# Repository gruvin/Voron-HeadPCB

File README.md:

# Voron-HeadPCB

## Oldschool wiring harness strapped to the back of the stepper where a CANN bus board might otherwise be.

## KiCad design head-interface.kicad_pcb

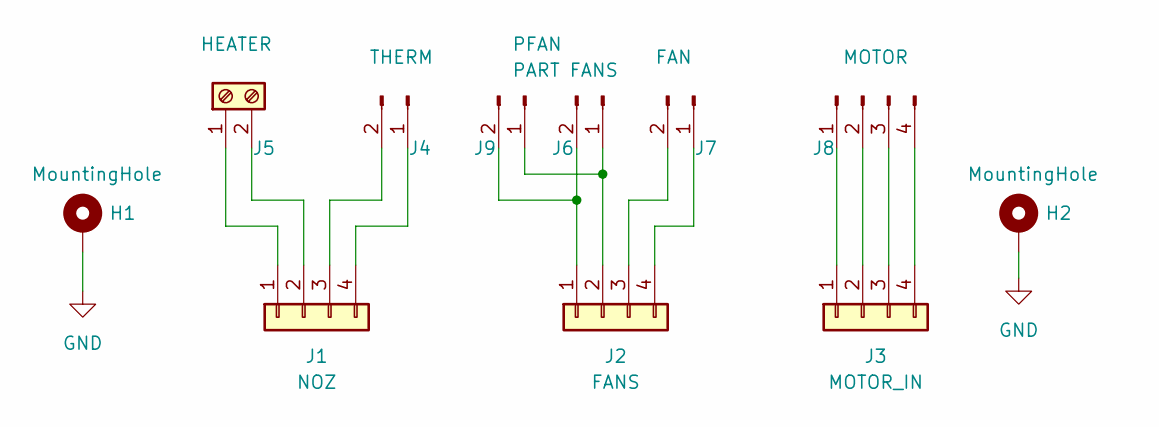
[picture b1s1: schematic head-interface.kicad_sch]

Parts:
H1, H2: MountingHole; MountingHole_3.2mm_M3_Pad
J1: NOZ; JST_EH_B4B-EH-A_1x04_P2.50mm_Vertical
J2: FANS; JST_EH_B4B-EH-A_1x04_P2.50mm_Vertical
J3: MOTOR_IN; JST_EH_B4B-EH-A_1x04_P2.50mm_Vertical
J4: THERM; JST_PH_B2B-PH-K_1x02_P2.00mm_Vertical
J5: HEATER; TerminalBlock_Phoenix_PT-1,5-2-3.5-H_1x02_P3.50mm_Horizontal
J6: PART FANS; JST_PH_B2B-PH-K_1x02_P2.00mm_Vertical
J7: FAN; JST_PH_B2B-PH-K_1x02_P2.00mm_Vertical
J8: MOTOR; JST_EH_B4B-EH-A_1x04_P2.50mm_Vertical
J9: PFAN; JST_PH_B2B-PH-K_1x02_P2.00mm_Vertical

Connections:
GND: H1.1, H2.1
unnamed: J1.1, J5.1
unnamed: J1.2, J5.2
unnamed: J1.3, J4.2
unnamed: J1.4, J4.1
unnamed: J2.1, J6.2, J9.2
unnamed: J2.2, J6.1, J9.1
unnamed: J2.3, J7.2
unnamed: J2.4, J7.1
unnamed: J3.1, J8.1
unnamed: J3.2, J8.2
unnamed: J3.3, J8.3
unnamed: J3.4, J8.4

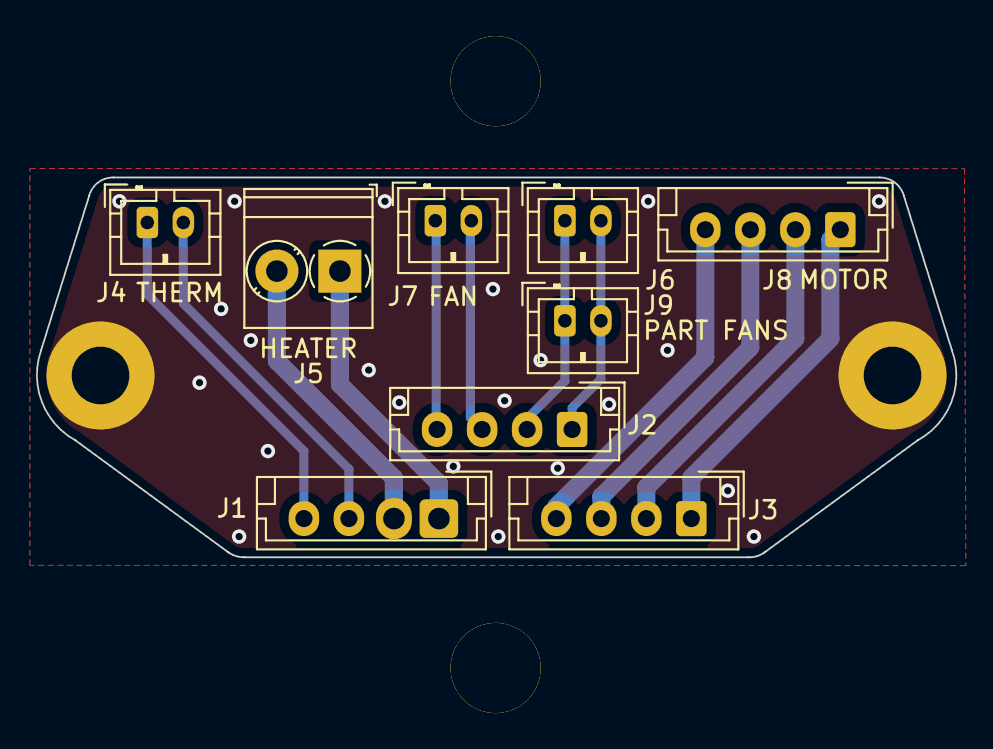
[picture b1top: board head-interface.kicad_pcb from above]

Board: 2 copper layers, 51.1 x 21.1 mm, 11 parts (0 on the bottom side), 13 nets.

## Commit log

2023-05-17 Second commit
2023-05-17 image
2023-05-17 production
2023-05-18 Add cam/ dir for pcb2gcode processing (see runcam.sh)
2023-05-18 imprived runcam.sh
2023-05-18 tweaks
2023-05-18 cam tweaks
2023-05-19 CAM now metric
2023-05-22 Increase heater wires hole size
2023-05-22 added 2nd part fan connector
2023-05-22 'final' tweaks :-)
